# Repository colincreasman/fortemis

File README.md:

# Fortemis ZMK Config

> **This branch:** [Forager with Sweep pinky stagger](design/forager-sweep-stagger/README.md).
> PCB, fabrication packages, both case styles and the shield use the new 34-key layout.
> The previous 36-key design remains on `main`. Physical fit is untested.

ZMK config for the Fortemis keyboard (Forager+Totem+FerrisSweep)

## Hardware design

Fortemis is designed from scratch with [Ergogen](https://docs.ergogen.xyz), KiCad and a
Forager-style enclosed case. It keeps the Forager's other column drops and two-thumb placement,
uses the Sweep's pinky-to-ring drop, and retains the 0/0/0/4/10-degree column splay. None
has been built yet, so nothing has been tried on hardware.

- [docs/requirements.md](docs/requirements.md): goals and requirements
- [docs/design-log.md](docs/design-log.md): design decisions and progress
- [docs/build-guide.md](docs/build-guide.md): parts list and how to build one
- `ergogen/`: the Ergogen layout config, footprints and build tools
- `pcb/`: KiCad 10 projects for both halves (routed); `pcb/fab/`: Gerber zips to order, and BOM and
  placement files for PCB assembly
- `case/`: STL files to print, a top and a base for each half, in two styles: the Forager-style
  [enclosed case](case/enclosed/README.md) and the Totemist-style [sandwich case](case/sandwich/README.md),
  whose rim comes up to the keycap tops ([compare them](case/README.md))

Rebuild the PCBs from `ergogen/config.yaml` (needs node, KiCad 10 and Java 25+):

```sh
python3 ergogen/tools/pcb.py build   # Ergogen -> pcb/*.kicad_pcb
python3 ergogen/tools/pcb.py route   # Freerouting + GND pours, then DRC (re-routed until clean)
python3 ergogen/tools/pcb.py drc     # DRC summary only
python3 ergogen/tools/pcb.py fab     # Gerbers + drill -> pcb/fab/*.zip, BOM + placement CSVs
```

Rebuild the cases from the PCBs (needs KiCad 10 and `pip install -r ergogen/tools/requirements.txt`):

```sh
python3 ergogen/tools/case.py            # enclosed case: case/enclosed/*.stl and docs/img/case.png
python3 ergogen/tools/case_sandwich.py   # sandwich case: case/sandwich/*
```

## Firmware

This repository is also the keyboard's [ZMK](https://zmk.dev) module and config, on ZMK v0.3.0.

- `boards/shields/fortemis/`: the shield: pins, keymap and the key layout ZMK Studio draws
- `build.yaml`: the firmware images to build; `config/west.yml`: ZMK and module versions
- [zmk-rgbled-widget](https://github.com/caksoylar/zmk-rgbled-widget) shows battery and connection
  status on the XIAO's RGB LED, which the case's light pipe carries to the USB-C end
- [ZMK Studio](https://zmk.dev/docs/features/studio) works with the left half (or the dongle),
  over USB or Bluetooth. Unlock it with the maintenance layer's U (below).

The keymap (`boards/shields/fortemis/fortemis.keymap`) is the owner's Forager keymap: QWERTY with
home-row mods and four layers. The two thumbs per half keep the Forager bindings:
Enter, Shift/Tab, number layer/Space, and Backspace. The former extra-thumb bindings are removed.
The media layer remains available through ZMK Studio remapping.

Holding both near thumbs (Enter + Backspace) gives the maintenance layer:

| Key | Does |
|---|---|
| Q or P, held 2 s | Reboots that half into its bootloader |
| T, held 2 s | Reboots the central (the left half, or the dongle in dongle mode) into its bootloader |
| A S D F G | Bluetooth profiles 0 to 4 |
| W | Clears the current Bluetooth profile |
| U | Unlocks ZMK Studio |

### Building

Push to GitHub: the *Build ZMK firmware* action builds every image, and the run's `firmware`
artifact holds the `.uf2` files. Or build them locally with Docker:

```sh
ergogen/tools/zmk_build.sh   # every image in build.yaml -> firmware/*.uf2
```

For this branch, isolated local validation writes to `firmware/forager-sweep-stagger/`:

```sh
FORTEMIS_ZMK_VOLUME=fortemis-forager-sweep-stagger \
FORTEMIS_FIRMWARE_OUTPUT="$PWD/firmware/forager-sweep-stagger" \
ergogen/tools/zmk_build.sh
```

The pin lists and Studio's key layout in the shield are generated from the PCBs, so re-run this
after changing a PCB (needs KiCad 10 and `pip install -r ergogen/tools/requirements.txt`):

```sh
python3 ergogen/tools/zmk.py           # update the shield from pcb/*.kicad_pcb
python3 ergogen/tools/zmk.py --check   # only check; fails if the shield and the PCBs differ
```

### Flashing

1. Plug the half into a computer and double-press its reset button. On an assembled half, press the
   lever in the case floor, near the USB-C port, twice. The XIAO shows up as a USB drive (usually
   named `XIAO-SENSE`).
2. Copy the half's `.uf2` file onto the drive. The half restarts with the new firmware.

| File | Flash to | Mode |
|---|---|---|
| `fortemis_left rgbled_adapter-seeeduino_xiao_ble-zmk.uf2` | left half | standalone |
| `fortemis_right rgbled_adapter-seeeduino_xiao_ble-zmk.uf2` | right half | **both** (the right half is a peripheral either way) |
| `fortemis_left_dongle_mode.uf2` | left half | dongle |
| `fortemis_dongle.uf2` | dongle | dongle |
| `settings_reset-seeeduino_xiao_ble-zmk.uf2` | either half | clears the half's Bluetooth pairings |
| `settings_reset_dongle.uf2` | dongle | clears the dongle's Bluetooth pairings |

In standalone mode the left half is the central: pair the computer with **Fortemis**. If the halves
don't connect to each other, flash the settings reset to both, then the firmware again.

The first time a half runs the firmware, it restarts once by itself. Two of the XIAO Plus's pads
(D14 and D15) are the chip's NFC antenna pins, and the firmware turns NFC off so that they work as
key inputs. That setting is stored in the chip, so it survives later flashing.

### Dongle mode (PandaKB USB dongle)

The keyboard can also run through
[PandaKB's ZMK dongle](https://pandakb.com/shop/keyboard-kit/pandakb-zmk-split-keyboard-dongle/)
(a nice!nano v2 with a 1.3" OLED), as the Forager does. The dongle becomes the central and both
halves its peripherals: plug it into a computer and the keyboard works as a USB keyboard, with no
Bluetooth pairing on that computer. ZMK fixes each part's role at build time, so switching modes
means reflashing.

- **Setup:** turn off other ZMK keyboards nearby, flash the settings reset to the dongle and both
  halves (the standalone pairings must be cleared first), then flash the dongle-mode firmware, plug
  in the dongle and turn both halves on. To go back, reset the halves and flash the standalone left
  firmware.
- Keymap changes then only need the dongle reflashed. To reach its bootloader without opening its
  case, use the maintenance layer's T.
- The dongle keeps all five Bluetooth profiles, so it can also pair to computers on its own battery,
  and ZMK Studio works with it. It never deep-sleeps: only a key press wakes a ZMK device, and the
  dongle has no keys.

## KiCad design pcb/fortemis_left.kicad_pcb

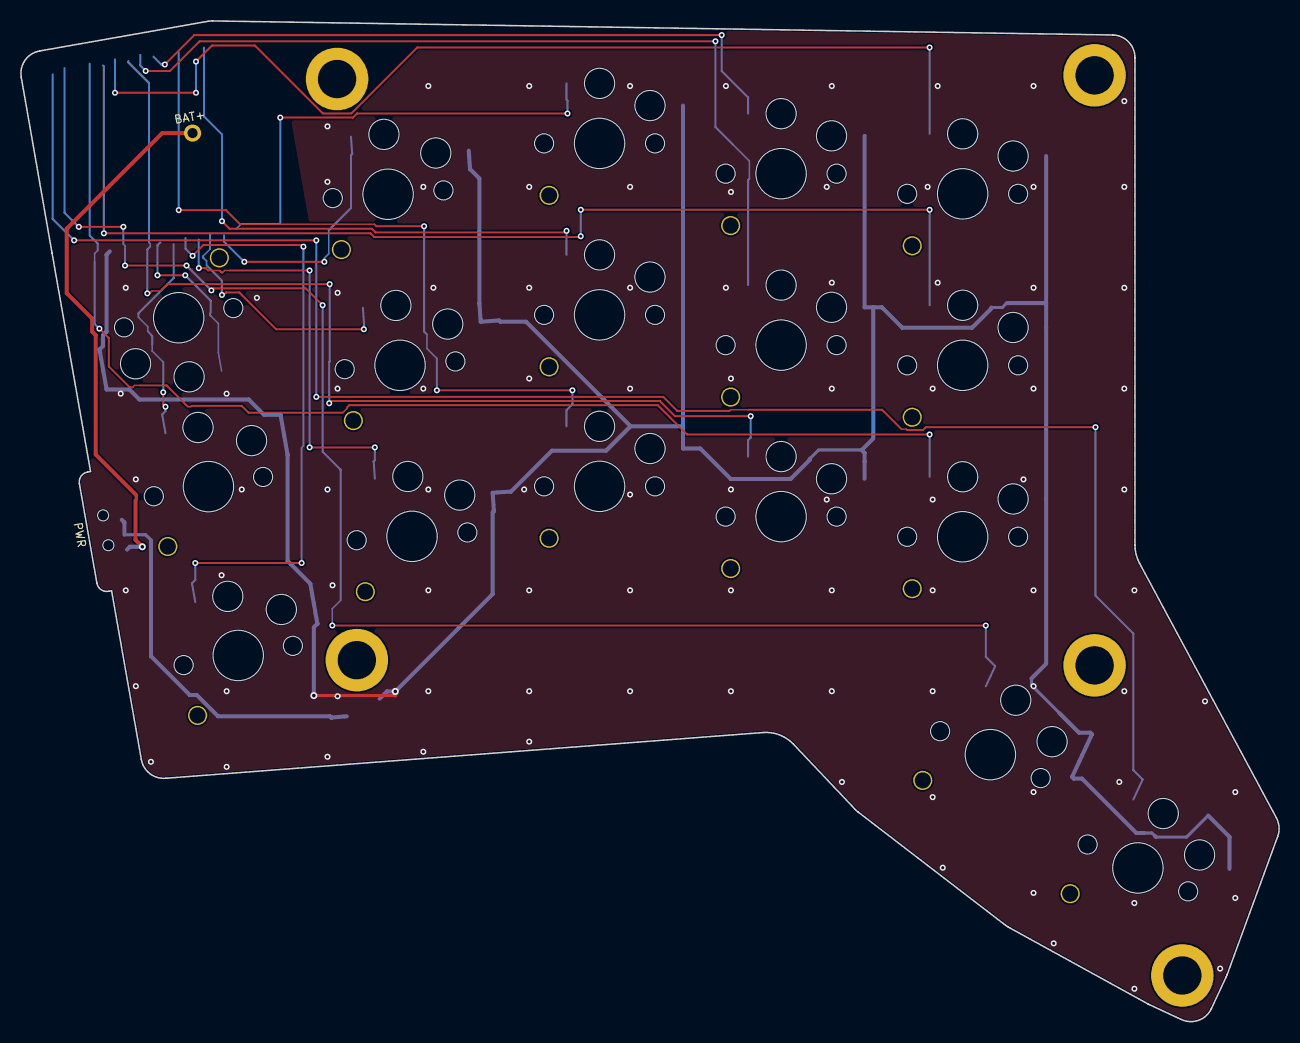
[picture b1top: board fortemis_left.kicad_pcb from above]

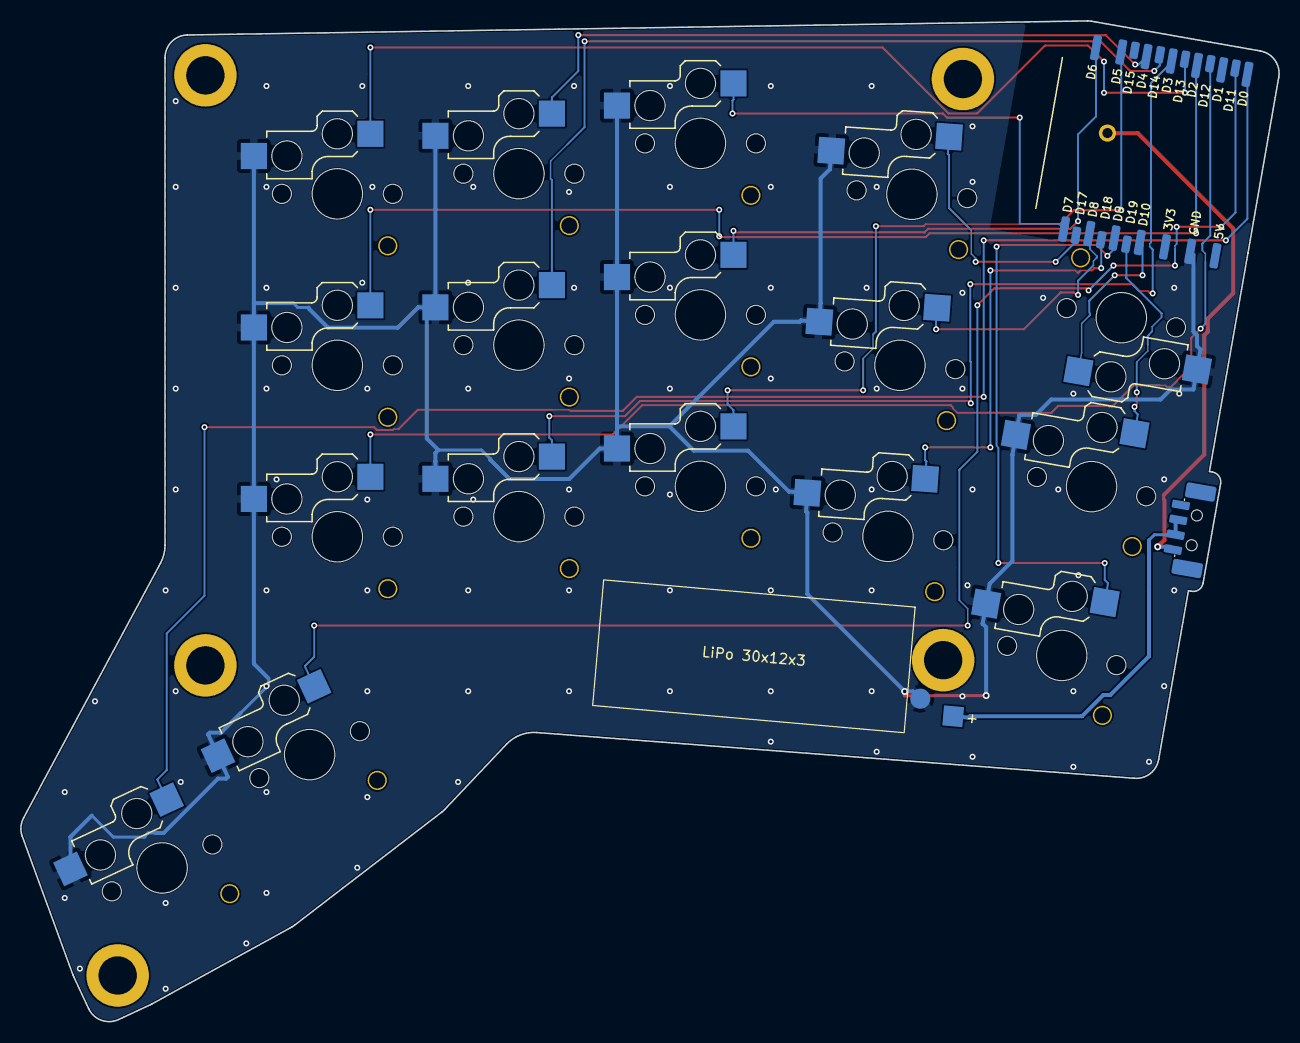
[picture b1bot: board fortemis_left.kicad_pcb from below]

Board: 2 copper layers, 124.7 x 99.2 mm, 25 parts (25 on the bottom side), 20 nets.

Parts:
BT1: LiPo 301230; battery_lipo_pads
MCU1: XIAO nRF52840 Plus; mcu_xiao_nrf52840_plus
NUT1, NUT2, NUT3, NUT4, NUT5: SMTSO2020MTJ; nut_smd_m2
PWR1: MSK12C02; power_switch_msk12c02_side
S1, S2, S3, S4, S5, S6, S7, S8, S9, S10, S11, S12, S13, S14, S15, S16, S17: switch_choc_v1_v2

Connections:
BAT_P: MCU1.BAT+, PWR1.1
BAT_RAW: BT1.1, PWR1.2
D0: MCU1.D0, S16.1
D2: MCU1.D2, S13.1
D3: MCU1.D3, S9.1
D4: MCU1.D4, S11.1
D5: MCU1.D5, S6.1
D6: MCU1.D6, S7.1
D7: MCU1.D7, S8.1
D8: MCU1.D8, S4.1
D9: MCU1.D9, S1.1
D10: MCU1.D10, S17.1
D11: MCU1.D11, S15.1
D12: MCU1.D12, S12.1
D13: MCU1.D13, S14.1
D14: MCU1.D14, S10.1
D17: MCU1.D17, S5.1
D18: MCU1.D18, S3.1
D19: MCU1.D19, S2.1
GND: BT1.2, MCU1.GND, S1.2, S2.2, S3.2, S4.2, S5.2, S6.2, S7.2, S8.2, S9.2, S10.2, S11.2, S12.2, S13.2, S14.2, S15.2, S16.2, S17.2

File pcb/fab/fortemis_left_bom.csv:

Comment,Designator,Footprint,LCSC Part #
Kailh Choc v1 hot-swap socket,"S1,S2,S3,S4,S5,S6,S7,S8,S9,S10,S11,S12,S13,S14,S15,S16,S17",CPG135001S30,C5333465
"M2 SMD nut, 2 mm","NUT1,NUT2,NUT3,NUT4,NUT5",SMTSO2020MTJ,C2916384
SPDT slide switch,PWR1,MSK12C02,C431540
